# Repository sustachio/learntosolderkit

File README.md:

# Electronics Club learn-to-solder kit

This was a learn to solder kit I developed for my school's electronics club consisting of an analog 3 note tunable keyboard with a 555 timer and piezo buzzer. More info can be found here: https://sethmueller.page/post/newspaper-article-hosting-a-learn-to-solder-day-at-lasa-electronics-club.

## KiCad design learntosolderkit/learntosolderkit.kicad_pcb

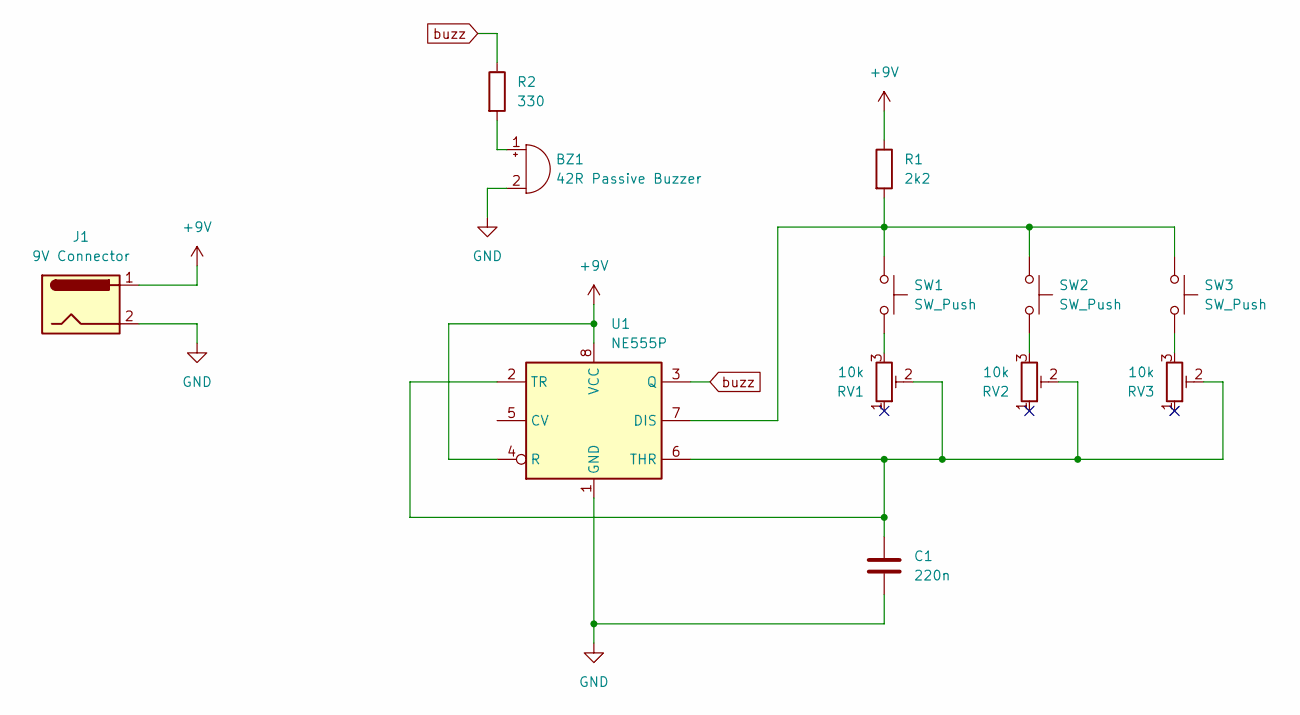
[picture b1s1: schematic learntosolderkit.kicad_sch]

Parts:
BZ1: 42R Passive Buzzer; HNB-09A05 buzzer
C1: 220n; C_Axial_L3.8mm_D2.6mm_P7.50mm_Horizontal
J1: 9V Connector; 9v_dc_batt_2_pin
R1: 2k2; R_Axial_DIN0207_L6.3mm_D2.5mm_P10.16mm_Horizontal
R2: 330; R_Axial_DIN0207_L6.3mm_D2.5mm_P10.16mm_Horizontal
RV1, RV2, RV3: 10k; 3386P_Trimmer
SW1, SW2, SW3: SW_Push; SW_PUSH_6mm
U1: NE555P; DIP-8_W7.62mm

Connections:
+9V: J1.1, R1.1, U1.4 (R), U1.8 (VCC)
GND: BZ1.2 (-), C1.2, J1.2, U1.1 (GND)
unnamed: BZ1.1 (+), R2.2
unnamed: RV1.3, SW1.2
unnamed: RV2.3, SW2.2
unnamed: RV3.3, SW3.2
unnamed: R1.2, SW1.1, SW2.1, SW3.1, U1.7 (DIS)
unnamed: C1.1, RV1.2, RV2.2, RV3.2, U1.2 (TR), U1.6 (THR)
buzz: R2.1, U1.3 (Q)

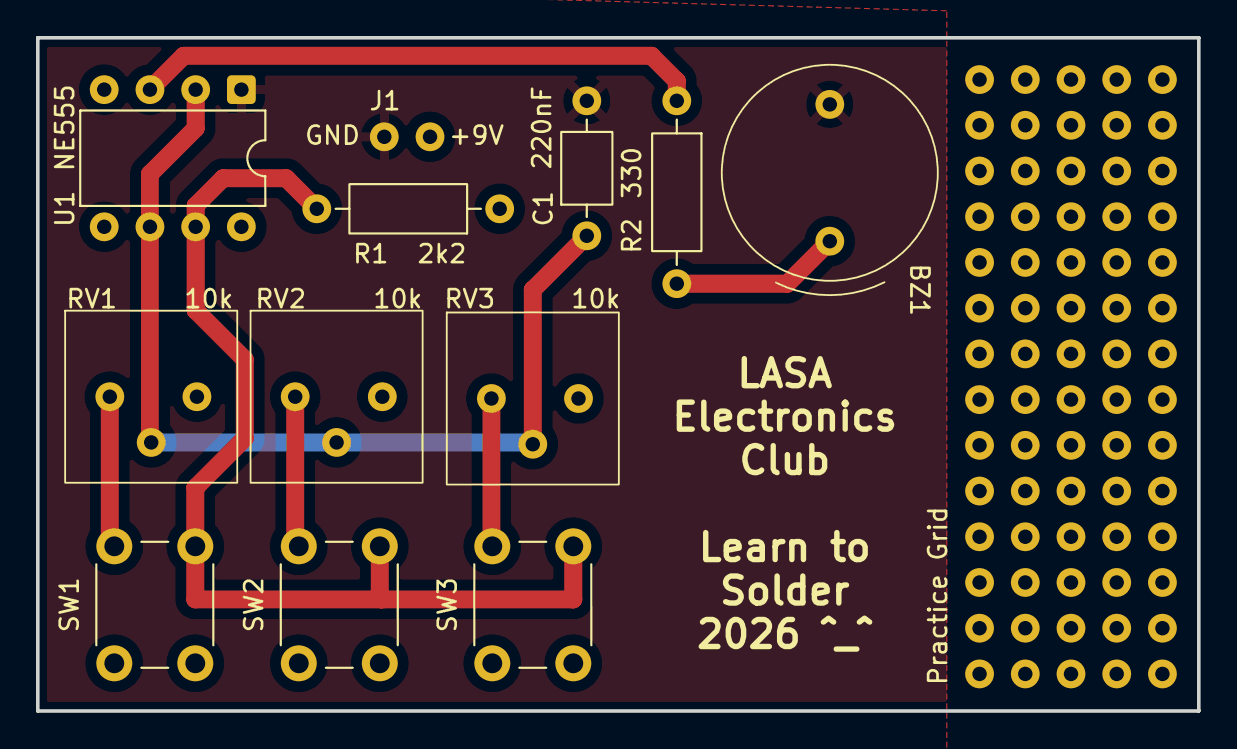
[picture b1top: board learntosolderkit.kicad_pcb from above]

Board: 2 copper layers, 64.5 x 37.4 mm, 12 parts (0 on the bottom side), 9 nets.

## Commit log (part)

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2025-12-02 create project
2025-12-02 add 555
2025-12-04 place components
2026-01-06 Finish up
